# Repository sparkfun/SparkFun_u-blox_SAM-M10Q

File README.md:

SparkFun GPS Breakout, Chip Antenna - SAM-M10Q (Qwiic)
========================================

[*SparkFun GPS Breakout, Chip Antenna - SAM-M10Q (Qwiic) (GPS-21834)*](https://www.sparkfun.com/products/21834)

The SparkFun SAM-M10Q GPS Breakout features the the SAM-M10Q chip-antenna module from u-blox<sup>&copy;</sup>. The SAM-M10Q can receive up to four GNSS constellations at once which improves time-to-fix and positional accuracy even in areas with limited view of the sky. The module includes a built-in chip antenna and is compatible with the L1 band on all five GNSS constellations (GPS L1 C/A, QZSS L1 C/A L1S, GLONASS L1OF, BeiDou B1C, and Galileo E1B/C). It has a horizontal position accuracy of 1.5 m, max update rate of 18 Hz when transmitting with just one GNSS constellation (max of 5Hz with 4 GNSS) and a cold start time to fix of 23 seconds. The board includes a rechargeable 3V/1mAh battery to provide backup power for up to four hours to maintain a hot start of just 1 second.

Repository Contents
-------------------

* **/Documentation** - Data sheets, additional product information
* **/Hardware** - Eagle design files (.brd, .sch)
* **/docs** - Hookup Guide files for the GPS Breakout, Chip Antenna - SAM-M10Q (Qwiic)
* **/Production** - Production panel files (.brd)

Documentation
--------------
* **[Library](https://github.com/sparkfun/SparkFun_u-blox_GNSS_v3)** - Arduino library for the SparkFun u-blox boards v3.
* **[Hookup Guide](https://docs.sparkfun.com/SparkFun_u-blox_SAM-M10Q)** - Basic hookup guide for the GPS Breakout, Chip Antenna - SAM-M10Q (Qwiic).

Product Versions
----------------

* [GPS-21834](https://www.sparkfun.com/products/21834) - Initial release of GPS Breakout, Chip Antenna - SAM-M10Q (Qwiic)

License Information
-------------------

This product is _**open source**_! 

Please review the LICENSE.md file for license information. 

If you have any questions or concerns on licensing, please contact technical support on our [SparkFun forums](https://forum.sparkfun.com/viewforum.php?f=152).

Distributed as-is; no warranty is given.

- Your friends at SparkFun.

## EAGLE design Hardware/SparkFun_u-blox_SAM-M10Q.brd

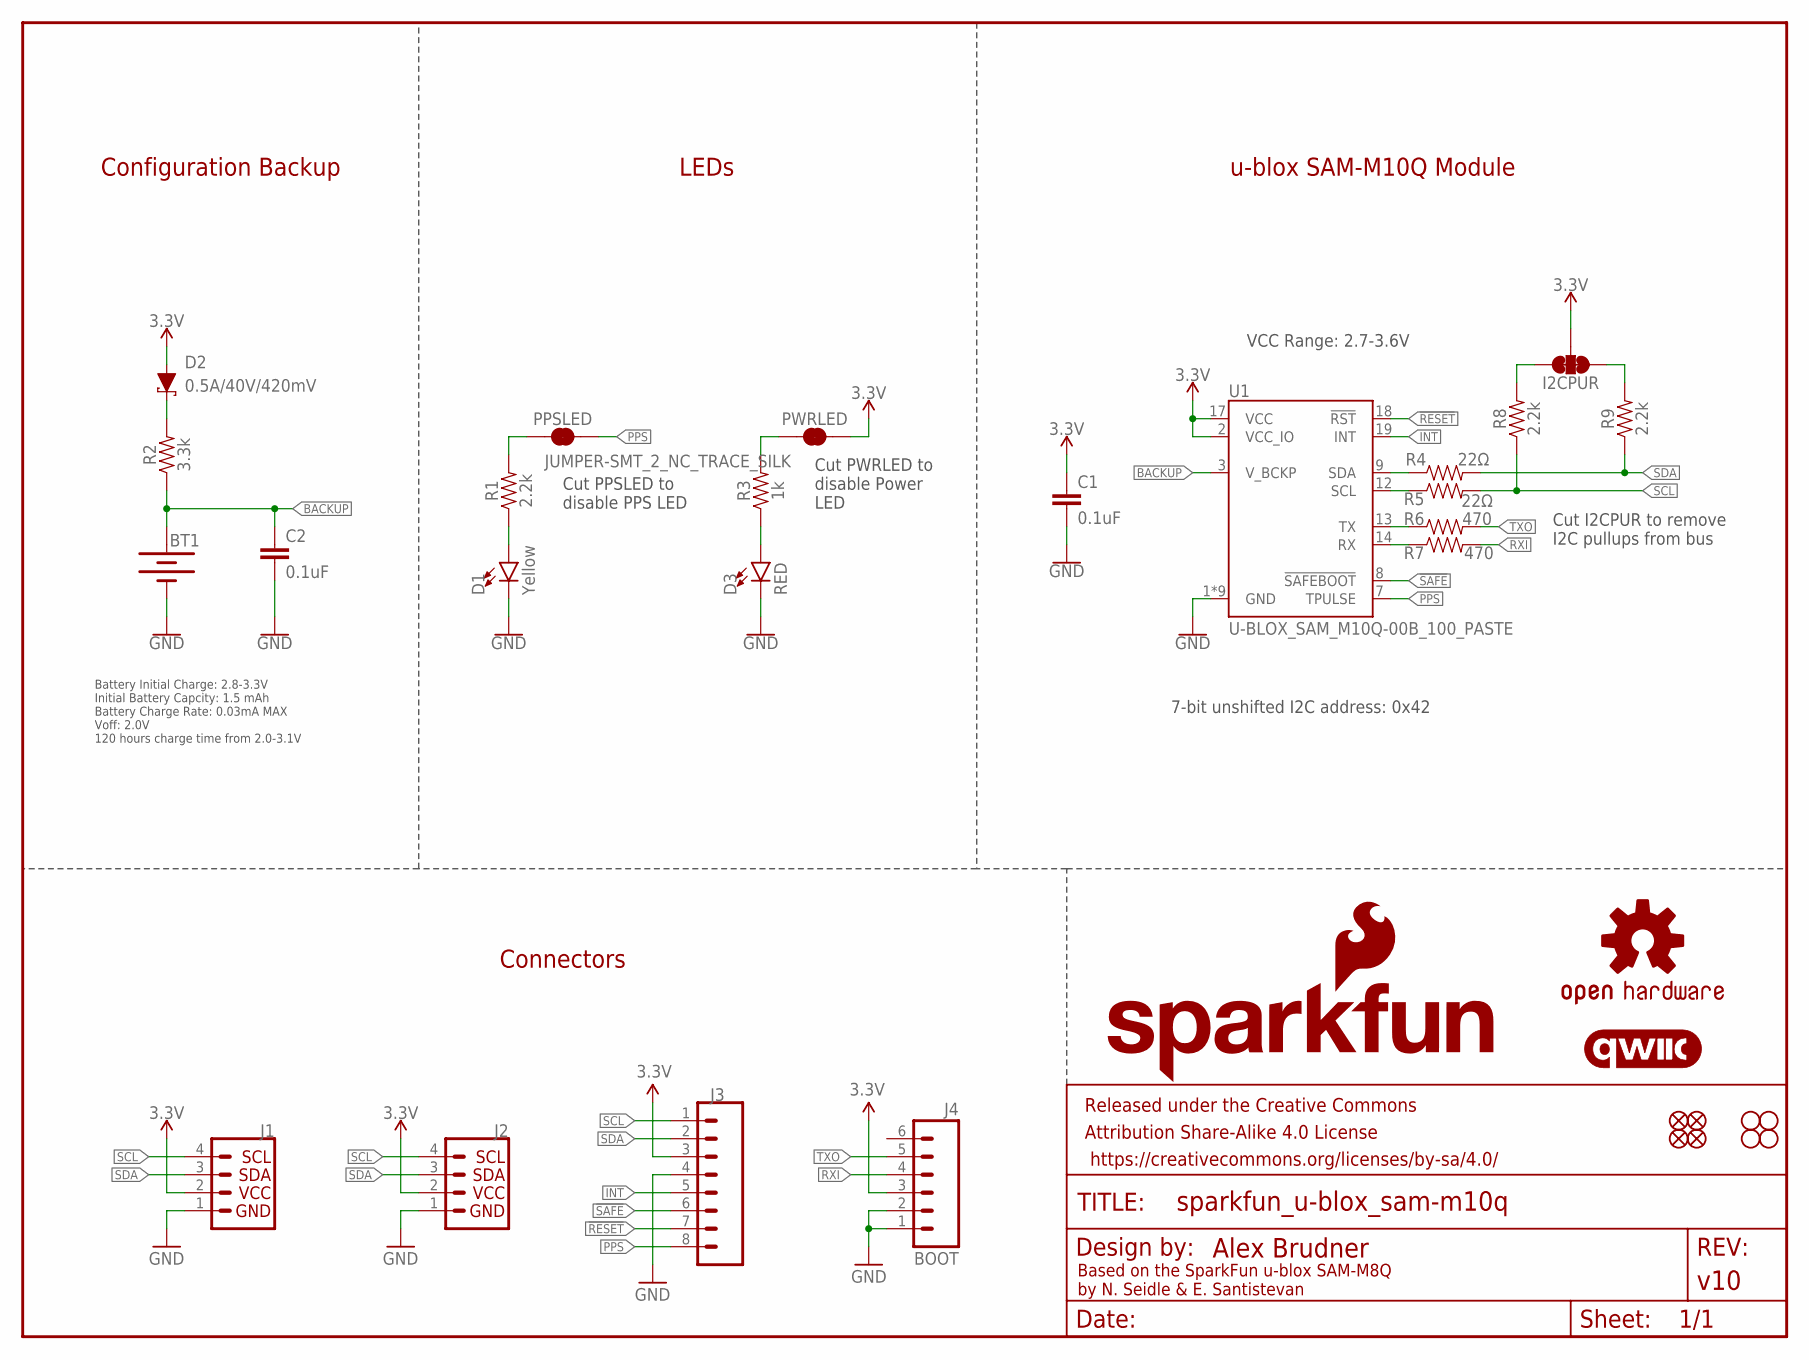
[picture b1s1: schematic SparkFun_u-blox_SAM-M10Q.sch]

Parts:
BT1: 6.8MM_COIN_CELL; MS421R_IV03E
C1, C2: 0.1uF; 0603
D1: Yellow; LED-0603
D2: 0.5A/40V/420mV; SOD-323
D3: RED; LED-0603
FD1, FD2, FD3, FD4: FIDUCIALUFIDUCIAL; FIDUCIAL-MICRO
FRAME1: FRAME-LETTER; CREATIVE_COMMONS
H1, H2, H3, H4: STAND-OFF
I2CPUR: JUMPER-SMT_3_2-NC_TRACE_SILK; SMT-JUMPER_3_2-NC_TRACE_SILK
J1, J2: Qwiic Right Angle; JST04_1MM_RA
J3: CONN_08NO_SILK_FEMALE_PTH; 1X08_NO_SILK
J4: BOOT; 1X06_NO_SILK
LOGO1: OSHW-LOGOM; OSHW-LOGO-M
LOGO2: SFE_LOGO_NAME_FLAME.2_INCH; SFE_LOGO_NAME_FLAME_.2
LOGO3: QWIIC_LOGO_CONNECTOR; QWIIC_5.5MM
PPSLED: JUMPER-SMT_2_NC_TRACE_SILK; SMT-JUMPER_2_NC_TRACE_SILK
PWRLED: JUMPER-SMT_2_NC_TRACE_SILK; SMT-JUMPER_2_NC_TRACE_SILK
R1, R8, R9: 2.2k; 0603
R2: 3.3k; 0603
R3: 1k; 0603
R4, R5: 22Ω; 0603
R6, R7: 470; 0603
U1: U-BLOX_SAM_M10Q-00B_100_PASTE; SAM-M10Q_100PASTE

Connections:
3.3V: C1.1, D2.A, I2CPUR.2, J1.2, J2.2, J3.3, J4.3, PWRLED.2, U1.2 (VCC_IO), U1.17 (VCC)
!RESET: J3.7, U1.18 (!RST)
!SAFE: J3.6, U1.8 (!SAFEBOOT)
BACKUP: BT1.+, C2.1, R2.1, U1.3 (V_BCKP)
GND: BT1.-, C1.2, C2.2, D1.C, D3.C, J1.1, J2.1, J3.4, J4.1, J4.2, U1.1 (GND), U1.4 (GND), U1.5 (GND), U1.6 (GND), U1.10 (GND), U1.11 (GND), U1.15 (GND), U1.16 (GND), U1.20 (GND)
INT: J3.5, U1.19 (INT)
unnamed: PWRLED.1, R3.2
unnamed: D1.A, R1.1
unnamed: D3.A, R3.1
unnamed: PPSLED.1, R1.2
unnamed: I2CPUR.1, R9.2
unnamed: D2.C, R2.2
unnamed: I2CPUR.3, R8.2
PPS: J3.8, PPSLED.2, U1.7 (TPULSE)
RXI: J4.4, R7.2
RXLV: R7.1, U1.14 (RX)
SCL: J1.4, J2.4, J3.1, R5.2, R8.1
SCL_LV: R5.1, U1.12 (SCL)
SDA: J1.3, J2.3, J3.2, R4.2, R9.1
SDA_LV: R4.1, U1.9 (SDA)
TXLV: R6.1, U1.13 (TX)
TXO: J4.5, R6.2

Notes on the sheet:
Based on the SparkFun u-blox SAM-M8Q by N. Seidle & E. Santistevan
Battery Initial Charge: 2.8-3.3V Initial Battery Capcity: 1.5 mAh Battery Charge Rate: 0.03mA MAX Voff: 2.0V 120 hours charge time from 2.0-3.1V
7-bit unshifted I2C address: 0x42
Cut I2CPUR to remove I2C pullups from bus
VCC Range: 2.7-3.6V
LEDs
Cut PPSLED to disable PPS LED
Cut PWRLED to disable Power LED
Configuration Backup
u-blox SAM-M10Q Module
Connectors

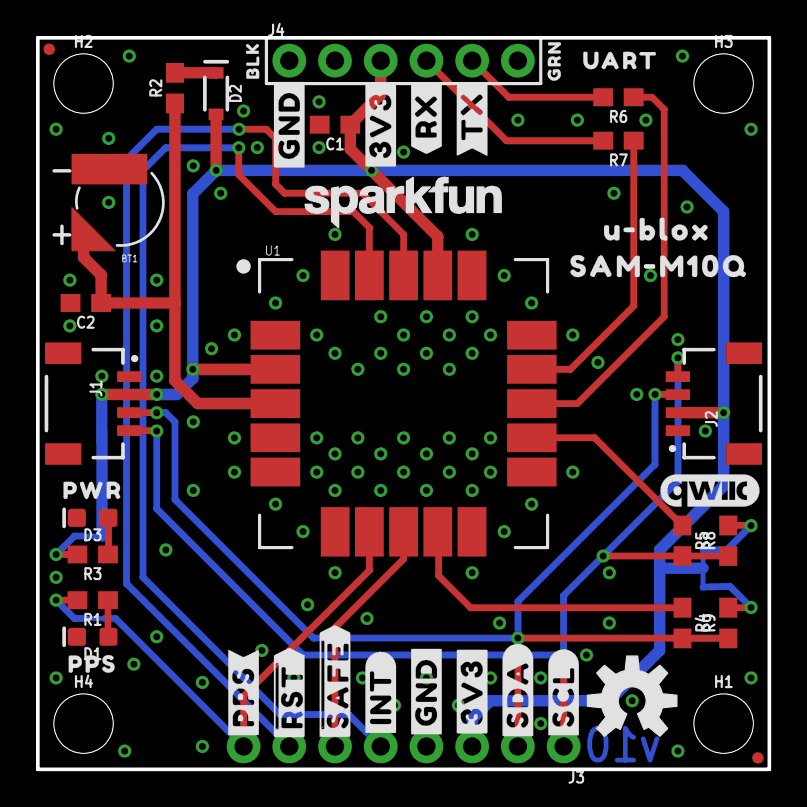
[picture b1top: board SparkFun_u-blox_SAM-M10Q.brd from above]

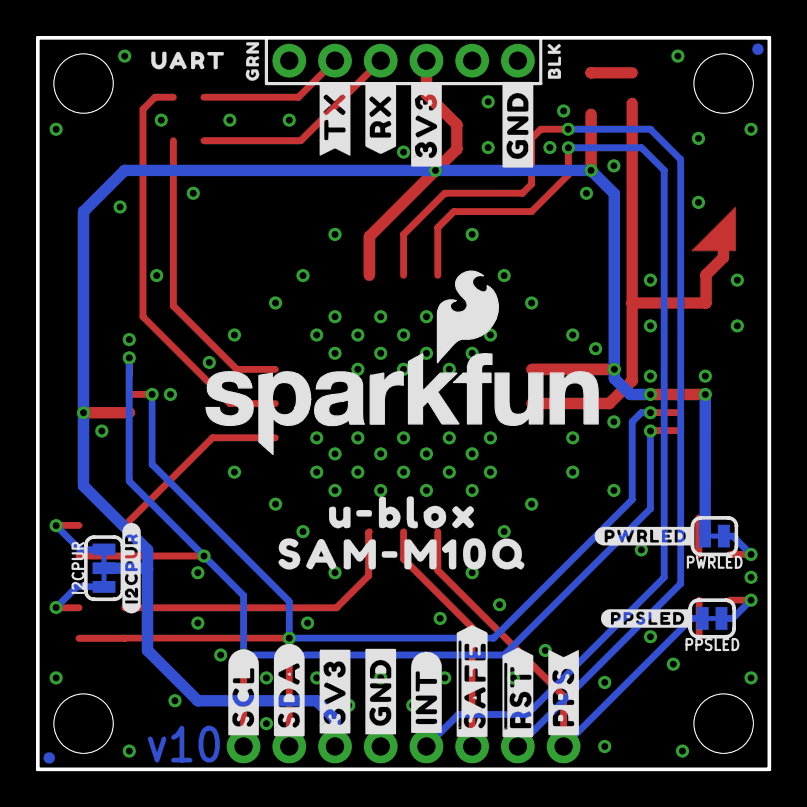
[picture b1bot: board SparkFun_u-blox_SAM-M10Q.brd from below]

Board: 2 copper layers, 40.6 x 40.6 mm, 76 parts (26 on the bottom side), 22 nets.

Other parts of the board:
U$1: SFE_LOGO_FLAME_STOP_.1
U$2: SAM#M10Q11
U$3, U$4: BLK4
U$5, U$6: GRN5
U$7, U$8: UART7
U$9: PPS9
U$10: PWR10
U$11, U$12: #TX#12
U$13, U$14: #RX#13
U$15, U$16, U$22, U$23: #3V3#0
U$17, U$20: #GND#4
U$18: U#BLOX11
U$19, U$21: #GND#5
U$24, U$25: #SCL#6
U$26, U$27: #SDA#7
U$28, U$29: #INT#8
U$30, U$33: ##RST##15
U$31: SFE_LOGO_NAME_.1
U$32: SAM#M10Q12
U$34, U$35: #PPS#13
U$36, U$37: ##SAFE##16
U$38: U#BLOX12
U$40: #PPSLED#0
U$41: #I2CPUR#0
U$42: #PWRLED#0

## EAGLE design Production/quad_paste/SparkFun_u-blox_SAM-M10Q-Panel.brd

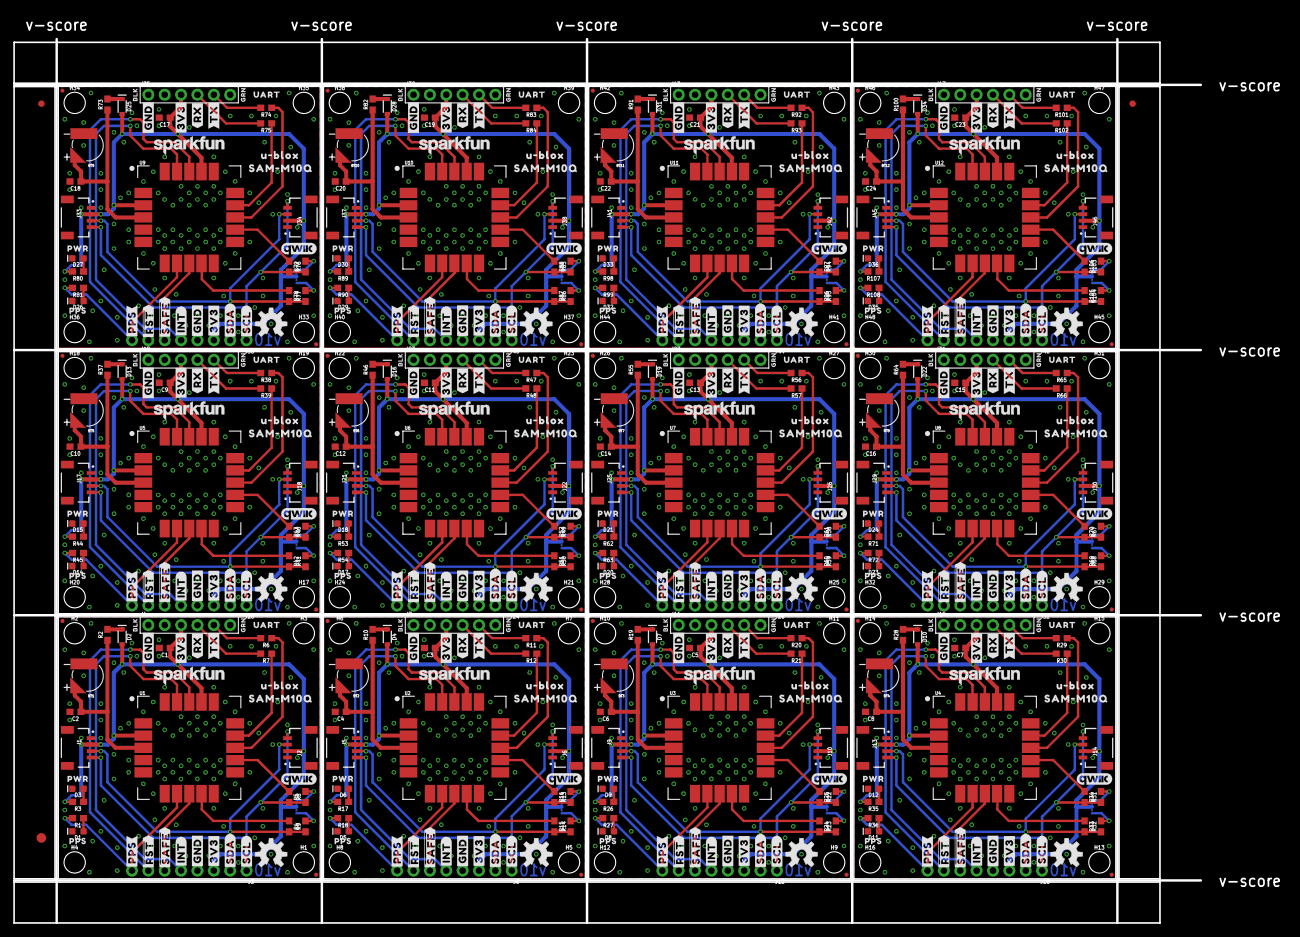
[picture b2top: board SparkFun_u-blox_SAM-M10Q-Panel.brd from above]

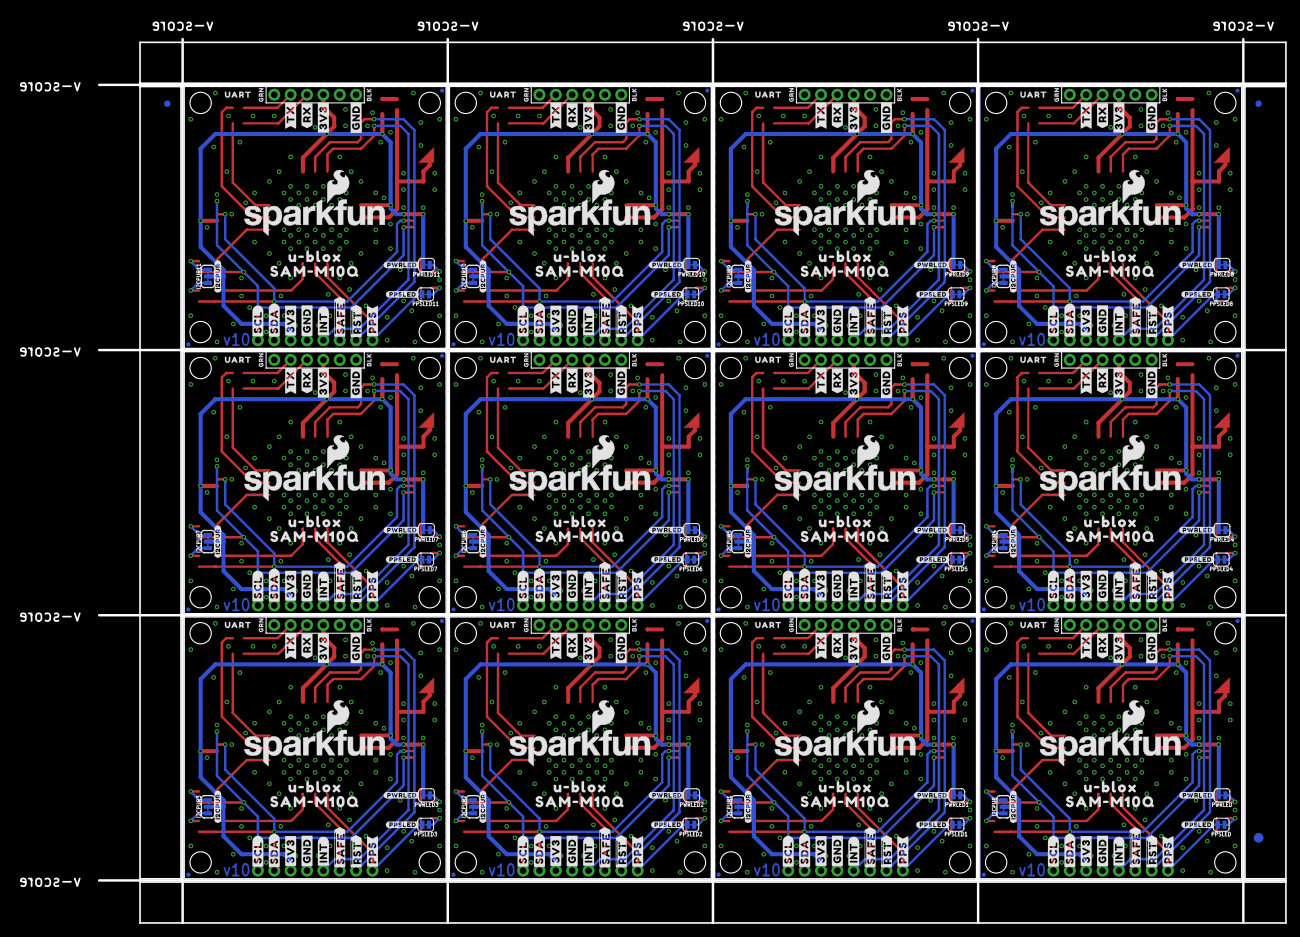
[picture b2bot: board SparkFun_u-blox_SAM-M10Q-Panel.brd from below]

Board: 2 copper layers, 197.3 x 141.0 mm, 906 parts (315 on the bottom side), 264 nets.

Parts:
BT1, BT2, BT3, BT4, BT5, BT6, BT7, BT8, BT9, BT10, BT11, BT12: 6.8MM_COIN_CELL; MS421R_IV03E
C1, C2, C3, C4, C5, C6, C7, C8, C9, C10, C11, C12, C13, C14, C15, C16, C17, C18, C19, C20, C21, C22, C23, C24: 0.1uF; 0603
D1, D5, D8, D11, D14, D17, D20, D23, D26, D29, D32, D35: Yellow; LED-0603
D2, D4, D7, D10, D13, D16, D19, D22, D25, D28, D31, D34: 0.5A/40V/420mV; SOD-323
D3, D6, D9, D12, D15, D18, D21, D24, D27, D30, D33, D36: RED; LED-0603
E$1, E$2, E$3, E$4: FIDUCIAL-1X2
E$5, E$6: FIDUCIAL-1.5X3
FD1, FD2, FD3, FD4, FD5, FD6, FD7, FD8, FD9, FD10, FD11, FD12, FD13, FD14, FD15, FD16, FD17, FD18, FD19, FD20, FD21, FD22, FD23, FD24, FD25, FD26, FD27, FD28, FD29, FD30, FD31, FD32, FD33, FD34, FD35, FD36, FD37, FD38, FD39, FD40, FD41, FD42, FD43, FD44, FD45, FD46, FD47, FD48: FIDUCIALUFIDUCIAL; FIDUCIAL-MICRO
H1, H2, H3, H4, H5, H6, H7, H8, H9, H10, H11, H12, H13, H14, H15, H16, H17, H18, H19, H20, H21, H22, H23, H24, H25, H26, H27, H28, H29, H30, H31, H32, H33, H34, H35, H36, H37, H38, H39, H40, H41, H42, H43, H44, H45, H46, H47, H48: STAND-OFF
I2CPUR, I2CPUR1, I2CPUR2, I2CPUR3, I2CPUR4, I2CPUR5, I2CPUR6, I2CPUR7, I2CPUR8, I2CPUR9, I2CPUR10, I2CPUR11: JUMPER-SMT_3_2-NC_TRACE_SILK; SMT-JUMPER_3_2-NC_TRACE_SILK
J1, J2, J5, J6, J9, J10, J13, J14, J17, J18, J21, J22, J25, J26, J29, J30, J33, J34, J37, J38, J41, J42, J45, J46: Qwiic Right Angle; JST04_1MM_RA
J3, J8, J12, J16, J20, J24, J28, J32, J36, J40, J44, J48: 1X08_NO_SILK
J4, J7, J11, J15, J19, J23, J27, J31, J35, J39, J43, J47: BOOT; 1X06_NO_SILK
LOGO1, LOGO4, LOGO7, LOGO10, LOGO13, LOGO16, LOGO19, LOGO22, LOGO25, LOGO28, LOGO31, LOGO34: OSHW-LOGOM; OSHW-LOGO-M
LOGO2, LOGO5, LOGO8, LOGO11, LOGO14, LOGO17, LOGO20, LOGO23, LOGO26, LOGO29, LOGO32, LOGO35: SFE_LOGO_NAME_FLAME.2_INCH; SFE_LOGO_NAME_FLAME_.2
LOGO3, LOGO6, LOGO9, LOGO12, LOGO15, LOGO18, LOGO21, LOGO24, LOGO27, LOGO30, LOGO33, LOGO36: QWIIC_LOGO_CONNECTOR; QWIIC_5.5MM
PPSLED, PPSLED1, PPSLED2, PPSLED3, PPSLED4, PPSLED5, PPSLED6, PPSLED7, PPSLED8, PPSLED9, PPSLED10, PPSLED11: SMT-JUMPER_2_NC_TRACE_SILK
PWRLED, PWRLED1, PWRLED2, PWRLED3, PWRLED4, PWRLED5, PWRLED6, PWRLED7, PWRLED8, PWRLED9, PWRLED10, PWRLED11: JUMPER-SMT_2_NC_TRACE_SILK; SMT-JUMPER_2_NC_TRACE_SILK
R1, R8, R9, R13, R14, R18, R22, R23, R27, R31, R32, R36, R40, R41, R45, R49, R50, R54, R58, R59, R63, R67, R68, R72, R76, R77, R81, R85, R86, R90, R94, R95, R99, R103, R104, R108: 2.2k; 0603
R2, R10, R19, R28, R37, R46, R55, R64, R73, R82, R91, R100: 3.3k; 0603
R3, R17, R26, R35, R44, R53, R62, R71, R80, R89, R98, R107: 1k; 0603
R4, R5, R15, R16, R24, R25, R33, R34, R42, R43, R51, R52, R60, R61, R69, R70, R78, R79, R87, R88, R96, R97, R105, R106: 22; 0603
R6, R7, R11, R12, R20, R21, R29, R30, R38, R39, R47, R48, R56, R57, R65, R66, R74, R75, R83, R84, R92, R93, R101, R102: 470; 0603
U1, U2, U3, U4, U5, U6, U7, U8, U9, U10, U11, U12: U-BLOX_SAM_M10Q-00B_QUAD_PASTE; SAM-M10Q_QUAD_PASTE
U$1, U$39, U$83, U$124, U$165, U$206, U$247, U$288, U$329, U$370, U$411, U$452: SFE_LOGO_FLAME_STOP_.1
U$2, U$79, U$120, U$161, U$202, U$243, U$284, U$325, U$366, U$407, U$448, U$489: SAM#M10Q11
U$3, U$4, U$43, U$44, U$84, U$85, U$125, U$126, U$166, U$167, U$207, U$208, U$248, U$249, U$289, U$290, U$330, U$331, U$371, U$372, U$412, U$413, U$453, U$454: BLK4
U$5, U$6, U$45, U$46, U$86, U$87, U$127, U$128, U$168, U$169, U$209, U$210, U$250, U$251, U$291, U$292, U$332, U$333, U$373, U$374, U$414, U$415, U$455, U$456: GRN5
U$7, U$8, U$47, U$48, U$88, U$89, U$129, U$130, U$170, U$171, U$211, U$212, U$252, U$253, U$293, U$294, U$334, U$335, U$375, U$376, U$416, U$417, U$457, U$458: UART7
U$9, U$49, U$90, U$131, U$172, U$213, U$254, U$295, U$336, U$377, U$418, U$459: PPS9
U$10, U$50, U$91, U$132, U$173, U$214, U$255, U$296, U$337, U$378, U$419, U$460: PWR10
U$11, U$12, U$51, U$52, U$92, U$93, U$133, U$134, U$174, U$175, U$215, U$216, U$256, U$257, U$297, U$298, U$338, U$339, U$379, U$380, U$420, U$421, U$461, U$462: #TX#12
U$13, U$14, U$53, U$54, U$94, U$95, U$135, U$136, U$176, U$177, U$217, U$218, U$258, U$259, U$299, U$300, U$340, U$341, U$381, U$382, U$422, U$423, U$463, U$464: #RX#13
U$15, U$16, U$22, U$23, U$55, U$56, U$61, U$62, U$96, U$97, U$102, U$103, U$137, U$138, U$143, U$144, U$178, U$179, U$184, U$185, U$219, U$220, U$225, U$226, U$260, U$261, U$266, U$267, U$301, U$302, U$307, U$308, U$342, U$343, U$348, U$349, U$383, U$384, U$389, U$390, U$424, U$425, U$430, U$431, U$465, U$466, U$471, U$472: #3V3#0
U$17, U$20, U$57, U$58, U$98, U$99, U$139, U$140, U$180, U$181, U$221, U$222, U$262, U$263, U$303, U$304, U$344, U$345, U$385, U$386, U$426, U$427, U$467, U$468: #GND#4
U$18, U$80, U$121, U$162, U$203, U$244, U$285, U$326, U$367, U$408, U$449, U$490: U#BLOX11
U$19, U$21, U$59, U$60, U$100, U$101, U$141, U$142, U$182, U$183, U$223, U$224, U$264, U$265, U$305, U$306, U$346, U$347, U$387, U$388, U$428, U$429, U$469, U$470: #GND#5
U$24, U$25, U$63, U$64, U$104, U$105, U$145, U$146, U$186, U$187, U$227, U$228, U$268, U$269, U$309, U$310, U$350, U$351, U$391, U$392, U$432, U$433, U$473, U$474: #SCL#6
U$26, U$27, U$65, U$66, U$106, U$107, U$147, U$148, U$188, U$189, U$229, U$230, U$270, U$271, U$311, U$312, U$352, U$353, U$393, U$394, U$434, U$435, U$475, U$476: #SDA#7
U$28, U$29, U$67, U$68, U$108, U$109, U$149, U$150, U$190, U$191, U$231, U$232, U$272, U$273, U$313, U$314, U$354, U$355, U$395, U$396, U$436, U$437, U$477, U$478: #INT#8
U$30, U$33, U$71, U$72, U$112, U$113, U$153, U$154, U$194, U$195, U$235, U$236, U$276, U$277, U$317, U$318, U$358, U$359, U$399, U$400, U$440, U$441, U$481, U$482: ##RST##15
U$31, U$75, U$116, U$157, U$198, U$239, U$280, U$321, U$362, U$403, U$444, U$485: SFE_LOGO_NAME_.1
U$32, U$81, U$122, U$163, U$204, U$245, U$286, U$327, U$368, U$409, U$450, U$491: SAM#M10Q12
U$34, U$35, U$69, U$70, U$110, U$111, U$151, U$152, U$192, U$193, U$233, U$234, U$274, U$275, U$315, U$316, U$356, U$357, U$397, U$398, U$438, U$439, U$479, U$480: #PPS#13
U$36, U$37, U$73, U$74, U$114, U$115, U$155, U$156, U$196, U$197, U$237, U$238, U$278, U$279, U$319, U$320, U$360, U$361, U$401, U$402, U$442, U$443, U$483, U$484: ##SAFE##16
U$38, U$82, U$123, U$164, U$205, U$246, U$287, U$328, U$369, U$410, U$451, U$492: U#BLOX12
U$40, U$77, U$118, U$159, U$200, U$241, U$282, U$323, U$364, U$405, U$446, U$487: #PPSLED#0
U$41, U$78, U$119, U$160, U$201, U$242, U$283, U$324, U$365, U$406, U$447, U$488: #I2CPUR#0
U$42, U$76, U$117, U$158, U$199, U$240, U$281, U$322, U$363, U$404, U$445, U$486: #PWRLED#0

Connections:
3.3V: C1.1, D2.A, I2CPUR.2, J1.2, J2.2, J3.3, J4.3, PWRLED.2, U1.2, U1.17
3.3V1: C3.1, D4.A, I2CPUR1.2, J5.2, J6.2, J7.3, J8.3, PWRLED1.2, U2.2, U2.17
3.3V2: C5.1, D7.A, I2CPUR2.2, J9.2, J10.2, J11.3, J12.3, PWRLED2.2, U3.2, U3.17
3.3V3: C7.1, D10.A, I2CPUR3.2, J13.2, J14.2, J15.3, J16.3, PWRLED3.2, U4.2, U4.17
3.3V4: C9.1, D13.A, I2CPUR4.2, J17.2, J18.2, J19.3, J20.3, PWRLED4.2, U5.2, U5.17
3.3V5: C11.1, D16.A, I2CPUR5.2, J21.2, J22.2, J23.3, J24.3, PWRLED5.2, U6.2, U6.17
3.3V6: C13.1, D19.A, I2CPUR6.2, J25.2, J26.2, J27.3, J28.3, PWRLED6.2, U7.2, U7.17
3.3V7: C15.1, D22.A, I2CPUR7.2, J29.2, J30.2, J31.3, J32.3, PWRLED7.2, U8.2, U8.17
3.3V8: C17.1, D25.A, I2CPUR8.2, J33.2, J34.2, J35.3, J36.3, PWRLED8.2, U9.2, U9.17
3.3V9: C19.1, D28.A, I2CPUR9.2, J37.2, J38.2, J39.3, J40.3, PWRLED9.2, U10.2, U10.17
3.3V10: C21.1, D31.A, I2CPUR10.2, J41.2, J42.2, J43.3, J44.3, PWRLED10.2, U11.2, U11.17
3.3V11: C23.1, D34.A, I2CPUR11.2, J45.2, J46.2, J47.3, J48.3, PWRLED11.2, U12.2, U12.17
!RESET: J3.7, U1.18
!RESET1: J8.7, U2.18
!RESET2: J12.7, U3.18
!RESET3: J16.7, U4.18
!RESET4: J20.7, U5.18
!RESET5: J24.7, U6.18
!RESET6: J28.7, U7.18
!RESET7: J32.7, U8.18
!RESET8: J36.7, U9.18
!RESET9: J40.7, U10.18
!RESET10: J44.7, U11.18
!RESET11: J48.7, U12.18
!SAFE: J3.6, U1.8
!SAFE1: J8.6, U2.8
!SAFE2: J12.6, U3.8
!SAFE3: J16.6, U4.8
!SAFE4: J20.6, U5.8
!SAFE5: J24.6, U6.8
!SAFE6: J28.6, U7.8
!SAFE7: J32.6, U8.8
!SAFE8: J36.6, U9.8
!SAFE9: J40.6, U10.8
!SAFE10: J44.6, U11.8
!SAFE11: J48.6, U12.8
BACKUP: BT1.+, C2.1, R2.1, U1.3
BACKUP1: BT2.+, C4.1, R10.1, U2.3
BACKUP2: BT3.+, C6.1, R19.1, U3.3
BACKUP3: BT4.+, C8.1, R28.1, U4.3
BACKUP4: BT5.+, C10.1, R37.1, U5.3
BACKUP5: BT6.+, C12.1, R46.1, U6.3
BACKUP6: BT7.+, C14.1, R55.1, U7.3
BACKUP7: BT8.+, C16.1, R64.1, U8.3
BACKUP8: BT9.+, C18.1, R73.1, U9.3
BACKUP9: BT10.+, C20.1, R82.1, U10.3
BACKUP10: BT11.+, C22.1, R91.1, U11.3
BACKUP11: BT12.+, C24.1, R100.1, U12.3
GND: BT1.-, C1.2, C2.2, D1.C, D3.C, J1.1, J2.1, J3.4, J4.1, J4.2, U1.1, U1.4, U1.5, U1.6, U1.10, U1.11, U1.15, U1.16, U1.20
GND1: BT2.-, C3.2, C4.2, D5.C, D6.C, J5.1, J6.1, J7.1, J7.2, J8.4, U2.1, U2.4, U2.5, U2.6, U2.10, U2.11, U2.15, U2.16, U2.20
GND2: BT3.-, C5.2, C6.2, D8.C, D9.C, J9.1, J10.1, J11.1, J11.2, J12.4, U3.1, U3.4, U3.5, U3.6, U3.10, U3.11, U3.15, U3.16, U3.20
GND3: BT4.-, C7.2, C8.2, D11.C, D12.C, J13.1, J14.1, J15.1, J15.2, J16.4, U4.1, U4.4, U4.5, U4.6, U4.10, U4.11, U4.15, U4.16, U4.20
GND4: BT5.-, C9.2, C10.2, D14.C, D15.C, J17.1, J18.1, J19.1, J19.2, J20.4, U5.1, U5.4, U5.5, U5.6, U5.10, U5.11, U5.15, U5.16, U5.20
GND5: BT6.-, C11.2, C12.2, D17.C, D18.C, J21.1, J22.1, J23.1, J23.2, J24.4, U6.1, U6.4, U6.5, U6.6, U6.10, U6.11, U6.15, U6.16, U6.20
GND6: BT7.-, C13.2, C14.2, D20.C, D21.C, J25.1, J26.1, J27.1, J27.2, J28.4, U7.1, U7.4, U7.5, U7.6, U7.10, U7.11, U7.15, U7.16, U7.20
GND7: BT8.-, C15.2, C16.2, D23.C, D24.C, J29.1, J30.1, J31.1, J31.2, J32.4, U8.1, U8.4, U8.5, U8.6, U8.10, U8.11, U8.15, U8.16, U8.20
GND8: BT9.-, C17.2, C18.2, D26.C, D27.C, J33.1, J34.1, J35.1, J35.2, J36.4, U9.1, U9.4, U9.5, U9.6, U9.10, U9.11, U9.15, U9.16, U9.20
GND9: BT10.-, C19.2, C20.2, D29.C, D30.C, J37.1, J38.1, J39.1, J39.2, J40.4, U10.1, U10.4, U10.5, U10.6, U10.10, U10.11, U10.15, U10.16, U10.20
GND10: BT11.-, C21.2, C22.2, D32.C, D33.C, J41.1, J42.1, J43.1, J43.2, J44.4, U11.1, U11.4, U11.5, U11.6, U11.10, U11.11, U11.15, U11.16, U11.20
GND11: BT12.-, C23.2, C24.2, D35.C, D36.C, J45.1, J46.1, J47.1, J47.2, J48.4, U12.1, U12.4, U12.5, U12.6, U12.10, U12.11, U12.15, U12.16, U12.20
INT: J3.5, U1.19
INT1: J8.5, U2.19
INT2: J12.5, U3.19
INT3: J16.5, U4.19
INT4: J20.5, U5.19
INT5: J24.5, U6.19
INT6: J28.5, U7.19
INT7: J32.5, U8.19
INT8: J36.5, U9.19
INT9: J40.5, U10.19
INT10: J44.5, U11.19
INT11: J48.5, U12.19
unnamed: PWRLED.1, R3.2
unnamed: D1.A, R1.1
unnamed: D3.A, R3.1
unnamed: PPSLED.1, R1.2
unnamed: I2CPUR.1, R9.2
unnamed: D2.C, R2.2
unnamed: D4.C, R10.2
unnamed: I2CPUR.3, R8.2
unnamed: I2CPUR1.1, R14.2
unnamed: I2CPUR1.3, R13.2
unnamed: D5.A, R18.1
unnamed: PPSLED1.1, R18.2
unnamed: PWRLED1.1, R17.2
unnamed: D6.A, R17.1
unnamed: D7.C, R19.2
unnamed: I2CPUR2.1, R23.2
unnamed: I2CPUR2.3, R22.2
unnamed: D8.A, R27.1
unnamed: PPSLED2.1, R27.2
unnamed: PWRLED2.1, R26.2
unnamed: D9.A, R26.1
unnamed: D10.C, R28.2
unnamed: I2CPUR3.1, R32.2
unnamed: I2CPUR3.3, R31.2
unnamed: D11.A, R36.1
unnamed: PPSLED3.1, R36.2
unnamed: PWRLED3.1, R35.2
unnamed: D12.A, R35.1
unnamed: D13.C, R37.2
unnamed: I2CPUR4.1, R41.2
unnamed: I2CPUR4.3, R40.2
unnamed: D14.A, R45.1
unnamed: PPSLED4.1, R45.2
unnamed: PWRLED4.1, R44.2
unnamed: D15.A, R44.1
unnamed: D16.C, R46.2
unnamed: I2CPUR5.1, R50.2
unnamed: I2CPUR5.3, R49.2
unnamed: D17.A, R54.1
unnamed: PPSLED5.1, R54.2
unnamed: PWRLED5.1, R53.2
unnamed: D18.A, R53.1
unnamed: D19.C, R55.2
unnamed: I2CPUR6.1, R59.2
unnamed: I2CPUR6.3, R58.2
unnamed: D20.A, R63.1
unnamed: PPSLED6.1, R63.2
unnamed: PWRLED6.1, R62.2
unnamed: D21.A, R62.1
unnamed: D22.C, R64.2
unnamed: I2CPUR7.1, R68.2
unnamed: I2CPUR7.3, R67.2
unnamed: D23.A, R72.1
unnamed: PPSLED7.1, R72.2
unnamed: PWRLED7.1, R71.2
unnamed: D24.A, R71.1
unnamed: D25.C, R73.2
unnamed: I2CPUR8.1, R77.2
unnamed: I2CPUR8.3, R76.2
unnamed: D26.A, R81.1
unnamed: PPSLED8.1, R81.2
unnamed: PWRLED8.1, R80.2
unnamed: D27.A, R80.1
unnamed: D28.C, R82.2
unnamed: I2CPUR9.1, R86.2
unnamed: I2CPUR9.3, R85.2
unnamed: D29.A, R90.1
unnamed: PPSLED9.1, R90.2
unnamed: PWRLED9.1, R89.2
unnamed: D30.A, R89.1
unnamed: D31.C, R91.2
unnamed: I2CPUR10.1, R95.2
unnamed: I2CPUR10.3, R94.2
unnamed: D32.A, R99.1
unnamed: PPSLED10.1, R99.2
unnamed: PWRLED10.1, R98.2
unnamed: D33.A, R98.1
unnamed: D34.C, R100.2
unnamed: I2CPUR11.1, R104.2
unnamed: I2CPUR11.3, R103.2
unnamed: D35.A, R108.1
unnamed: PPSLED11.1, R108.2
unnamed: PWRLED11.1, R107.2
unnamed: D36.A, R107.1
PPS: J3.8, PPSLED.2, U1.7
PPS1: J8.8, PPSLED1.2, U2.7
PPS2: J12.8, PPSLED2.2, U3.7
PPS3: J16.8, PPSLED3.2, U4.7
PPS4: J20.8, PPSLED4.2, U5.7
PPS5: J24.8, PPSLED5.2, U6.7
PPS6: J28.8, PPSLED6.2, U7.7
PPS7: J32.8, PPSLED7.2, U8.7
PPS8: J36.8, PPSLED8.2, U9.7
PPS9: J40.8, PPSLED9.2, U10.7
PPS10: J44.8, PPSLED10.2, U11.7
PPS11: J48.8, PPSLED11.2, U12.7
RXI: J4.4, R7.2
RXI1: J7.4, R12.2
RXI2: J11.4, R21.2
RXI3: J15.4, R30.2
RXI4: J19.4, R39.2
RXI5: J23.4, R48.2
RXI6: J27.4, R57.2
RXI7: J31.4, R66.2
RXI8: J35.4, R75.2
RXI9: J39.4, R84.2
RXI10: J43.4, R93.2
RXI11: J47.4, R102.2
RXLV: R7.1, U1.14
RXLV1: R12.1, U2.14
RXLV2: R21.1, U3.14
RXLV3: R30.1, U4.14
RXLV4: R39.1, U5.14
RXLV5: R48.1, U6.14
RXLV6: R57.1, U7.14
RXLV7: R66.1, U8.14
RXLV8: R75.1, U9.14
RXLV9: R84.1, U10.14
RXLV10: R93.1, U11.14
RXLV11: R102.1, U12.14
SCL: J1.4, J2.4, J3.1, R5.2, R8.1
SCL1: J5.4, J6.4, J8.1, R13.1, R16.2
SCL2: J9.4, J10.4, J12.1, R22.1, R25.2
SCL3: J13.4, J14.4, J16.1, R31.1, R34.2
SCL4: J17.4, J18.4, J20.1, R40.1, R43.2
SCL5: J21.4, J22.4, J24.1, R49.1, R52.2
SCL6: J25.4, J26.4, J28.1, R58.1, R61.2
SCL7: J29.4, J30.4, J32.1, R67.1, R70.2
SCL8: J33.4, J34.4, J36.1, R76.1, R79.2
SCL9: J37.4, J38.4, J40.1, R85.1, R88.2
SCL10: J41.4, J42.4, J44.1, R94.1, R97.2
SCL11: J45.4, J46.4, J48.1, R103.1, R106.2
SCL_LV: R5.1, U1.12
SCL_LV1: R16.1, U2.12
SCL_LV2: R25.1, U3.12
SCL_LV3: R34.1, U4.12
SCL_LV4: R43.1, U5.12
SCL_LV5: R52.1, U6.12
SCL_LV6: R61.1, U7.12
SCL_LV7: R70.1, U8.12
SCL_LV8: R79.1, U9.12
SCL_LV9: R88.1, U10.12
SCL_LV10: R97.1, U11.12
SCL_LV11: R106.1, U12.12
SDA: J1.3, J2.3, J3.2, R4.2, R9.1
SDA1: J5.3, J6.3, J8.2, R14.1, R15.2
SDA2: J9.3, J10.3, J12.2, R23.1, R24.2
SDA3: J13.3, J14.3, J16.2, R32.1, R33.2
SDA4: J17.3, J18.3, J20.2, R41.1, R42.2
SDA5: J21.3, J22.3, J24.2, R50.1, R51.2
SDA6: J25.3, J26.3, J28.2, R59.1, R60.2
SDA7: J29.3, J30.3, J32.2, R68.1, R69.2
SDA8: J33.3, J34.3, J36.2, R77.1, R78.2
SDA9: J37.3, J38.3, J40.2, R86.1, R87.2
SDA10: J41.3, J42.3, J44.2, R95.1, R96.2
SDA11: J45.3, J46.3, J48.2, R104.1, R105.2
SDA_LV: R4.1, U1.9
SDA_LV1: R15.1, U2.9
SDA_LV2: R24.1, U3.9
SDA_LV3: R33.1, U4.9
SDA_LV4: R42.1, U5.9
SDA_LV5: R51.1, U6.9
SDA_LV6: R60.1, U7.9
SDA_LV7: R69.1, U8.9
SDA_LV8: R78.1, U9.9
SDA_LV9: R87.1, U10.9
SDA_LV10: R96.1, U11.9
SDA_LV11: R105.1, U12.9
TXLV: R6.1, U1.13
TXLV1: R11.1, U2.13
TXLV2: R20.1, U3.13
TXLV3: R29.1, U4.13
TXLV4: R38.1, U5.13
TXLV5: R47.1, U6.13
TXLV6: R56.1, U7.13
TXLV7: R65.1, U8.13
TXLV8: R74.1, U9.13
TXLV9: R83.1, U10.13
TXLV10: R92.1, U11.13
TXLV11: R101.1, U12.13
TXO: J4.5, R6.2
TXO1: J7.5, R11.2
TXO2: J11.5, R20.2
TXO3: J15.5, R29.2
TXO4: J19.5, R38.2
TXO5: J23.5, R47.2
TXO6: J27.5, R56.2
TXO7: J31.5, R65.2
TXO8: J35.5, R74.2
TXO9: J39.5, R83.2
TXO10: J43.5, R92.2
TXO11: J47.5, R101.2

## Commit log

2023-02-13 Remove unnecessary folders from template.
2023-02-13 Added Datasheet/Integration Manual
2023-02-13 Add schematic, board, module lib.
    v01 of board complete.
2023-02-13 Update for v10, Panelize. Add measures.
2023-02-14 Update post design review.
    Swap for updated reflowable battery.
    Adjust note for battery accordingly.
    Add qwiic symbol in schematic, replacing silk only on board.
    Expand t/b keepout under M10Q.
    Swap SCL/SDA silk so they are on the correct pins.
2023-02-14 Rework paste for DFM experiment.
    Move original panel into 100_paste folder.
    Repanelize with quad box paste and put into quad_paste folder.
    Update library to have new variant.
    Update sch and brd with new part.
2023-03-31 Update README.md
    Updating README.md from template.
2023-04-03 Documentation
    Initial Hookup Guide commit.
2023-04-05 URL updates & other tweaks
    Updating guide URL along with fixing filepath errors/folder misplacements.
2023-04-05 Update mkdocs.yml
    Fixing overrides custom_dir error.
2023-04-05 Update for release
    Remove quad paste part from lib.
    Remove quad paste production folder.
    Move 100 paste up one folder.
    Update schematic/board for new part.
2023-04-05 Delete Firmware folder
    None here, see SparkFun GNSS v3 library.
2023-04-05 Update Hardcopy
    Fix filepath
2023-04-06 Update mkdocs.yml
    Changing pages build branch from main to docs.
2023-04-06 Update Introduction.md
    Fix Qwiic image link.
2023-04-06 Update tables
    Updating multi-GNSS specs table.
2023-04-06 Fixing Single Page
    Fixing single page render errors.
2023-04-12 Update intro
    Fixing grid cards rendering for suggested reading.
2023-04-13 Post-Launch Fixes
    Fixing suggested reading image sizing. Adding Firmware Description doc & link. Removing Firmware Folder to match main branch.
2023-05-17 Update README.md
    Fixing product version link.
2023-07-26 Update introduction.md
    Updating Qwiic cable kit photo link
2023-07-26 Deployed d886846 with MkDocs version: 1.4.3
2024-06-04 Deployed f13f3d9 with MkDocs version: 1.6.0

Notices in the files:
parts and their libraries:
SparkFun-Aesthetics: Licensing: Creative Commons ShareAlike 4.0 International - https://creativecommons.org/licenses/by-sa/4.0
SparkFun-Aesthetics: Released under the Creative Commons Attribution Share-Alike 4.0 License
SparkFun-Aesthetics: https://creativecommons.org/licenses/by-sa/4.0
